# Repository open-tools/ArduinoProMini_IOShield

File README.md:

# ArduinoProMini_IOShield

Quick prototyping breakout board for Arduino Pro Mini with interface for NRF24L01+ and RFM69H wireless modules and breadboards and/or I²C connectors

## Inspiration
This board is inspired by the Arduino "Nano IO Shields" available for cheap at aliexpress (search for "arduino nano nrf24l01 board", e.g. [here](https://www.aliexpress.com/item/Free-shipping-Nano-328P-IO-wireless-sensor-expansion-board-for-XBEE-and-NRF24L01-Socket-for-arduino/32298692903.html)), which provide breakout pins, a connector for an NRF24L01+ module and an XBee module. 
As I don't have any use for the XBee socket, I simply broke off the header pins and instead taped a [tiny 5x11 pin breadboard](https://www.aliexpress.com/item/7Pcs-Mini-55-Points-Breadboard-Solderless-Prototype-Tie-point-For-Arduino-GM/32670910749.html) to the board. 

These boards are perfect for quick prototyping for the MySensors project for several reasons:
* you have the nrf24l01+ radio module already wired with their own voltage regulators and level shifters
* The board has its own power input and voltage regulators (VCC 5V will be fed to the Nano), so sensors with a high current requirement will get the power directly from the supply and not through the Arduino board.
* Each analog and digital pin has its own VCC+GND pins (usually when working with multiple sensors there is a severe shortage of VCC/GND pins for each sensor)
* The I²C and serial (RX/TX) lines are readily available as 1x4 pin headers (i.e. you don't need to know whether A4 or A5 is SDA or SCL).

The only drawback is that I use Pro Minis for most of my projects, so prototyping with a Nano means you are never testing the actual board in the prototype.

## The Board

This board provides 
* each pin of the Arduino Pro Mini as a pin header with its own VCC and GND 
* pads/connectors for a NRF24L01+ or a RFM69H wireless module (and solder pads for an XC6206 5V->3.3V regulator if required)
* I²C connector (VCC, GND, SCL, SDA)
* space for a tiny 55-pin mini breakout board or alternative three additional I²C breakout connections
* solder pads for its own AMS1117 voltage regulator
* ICSP connector to program the bootloader
* drills for the Arduino large enough to fit PogoPins, too, and
* the board outline and the holes are identical to the Arduino Uno, so Arduino holders can be used.

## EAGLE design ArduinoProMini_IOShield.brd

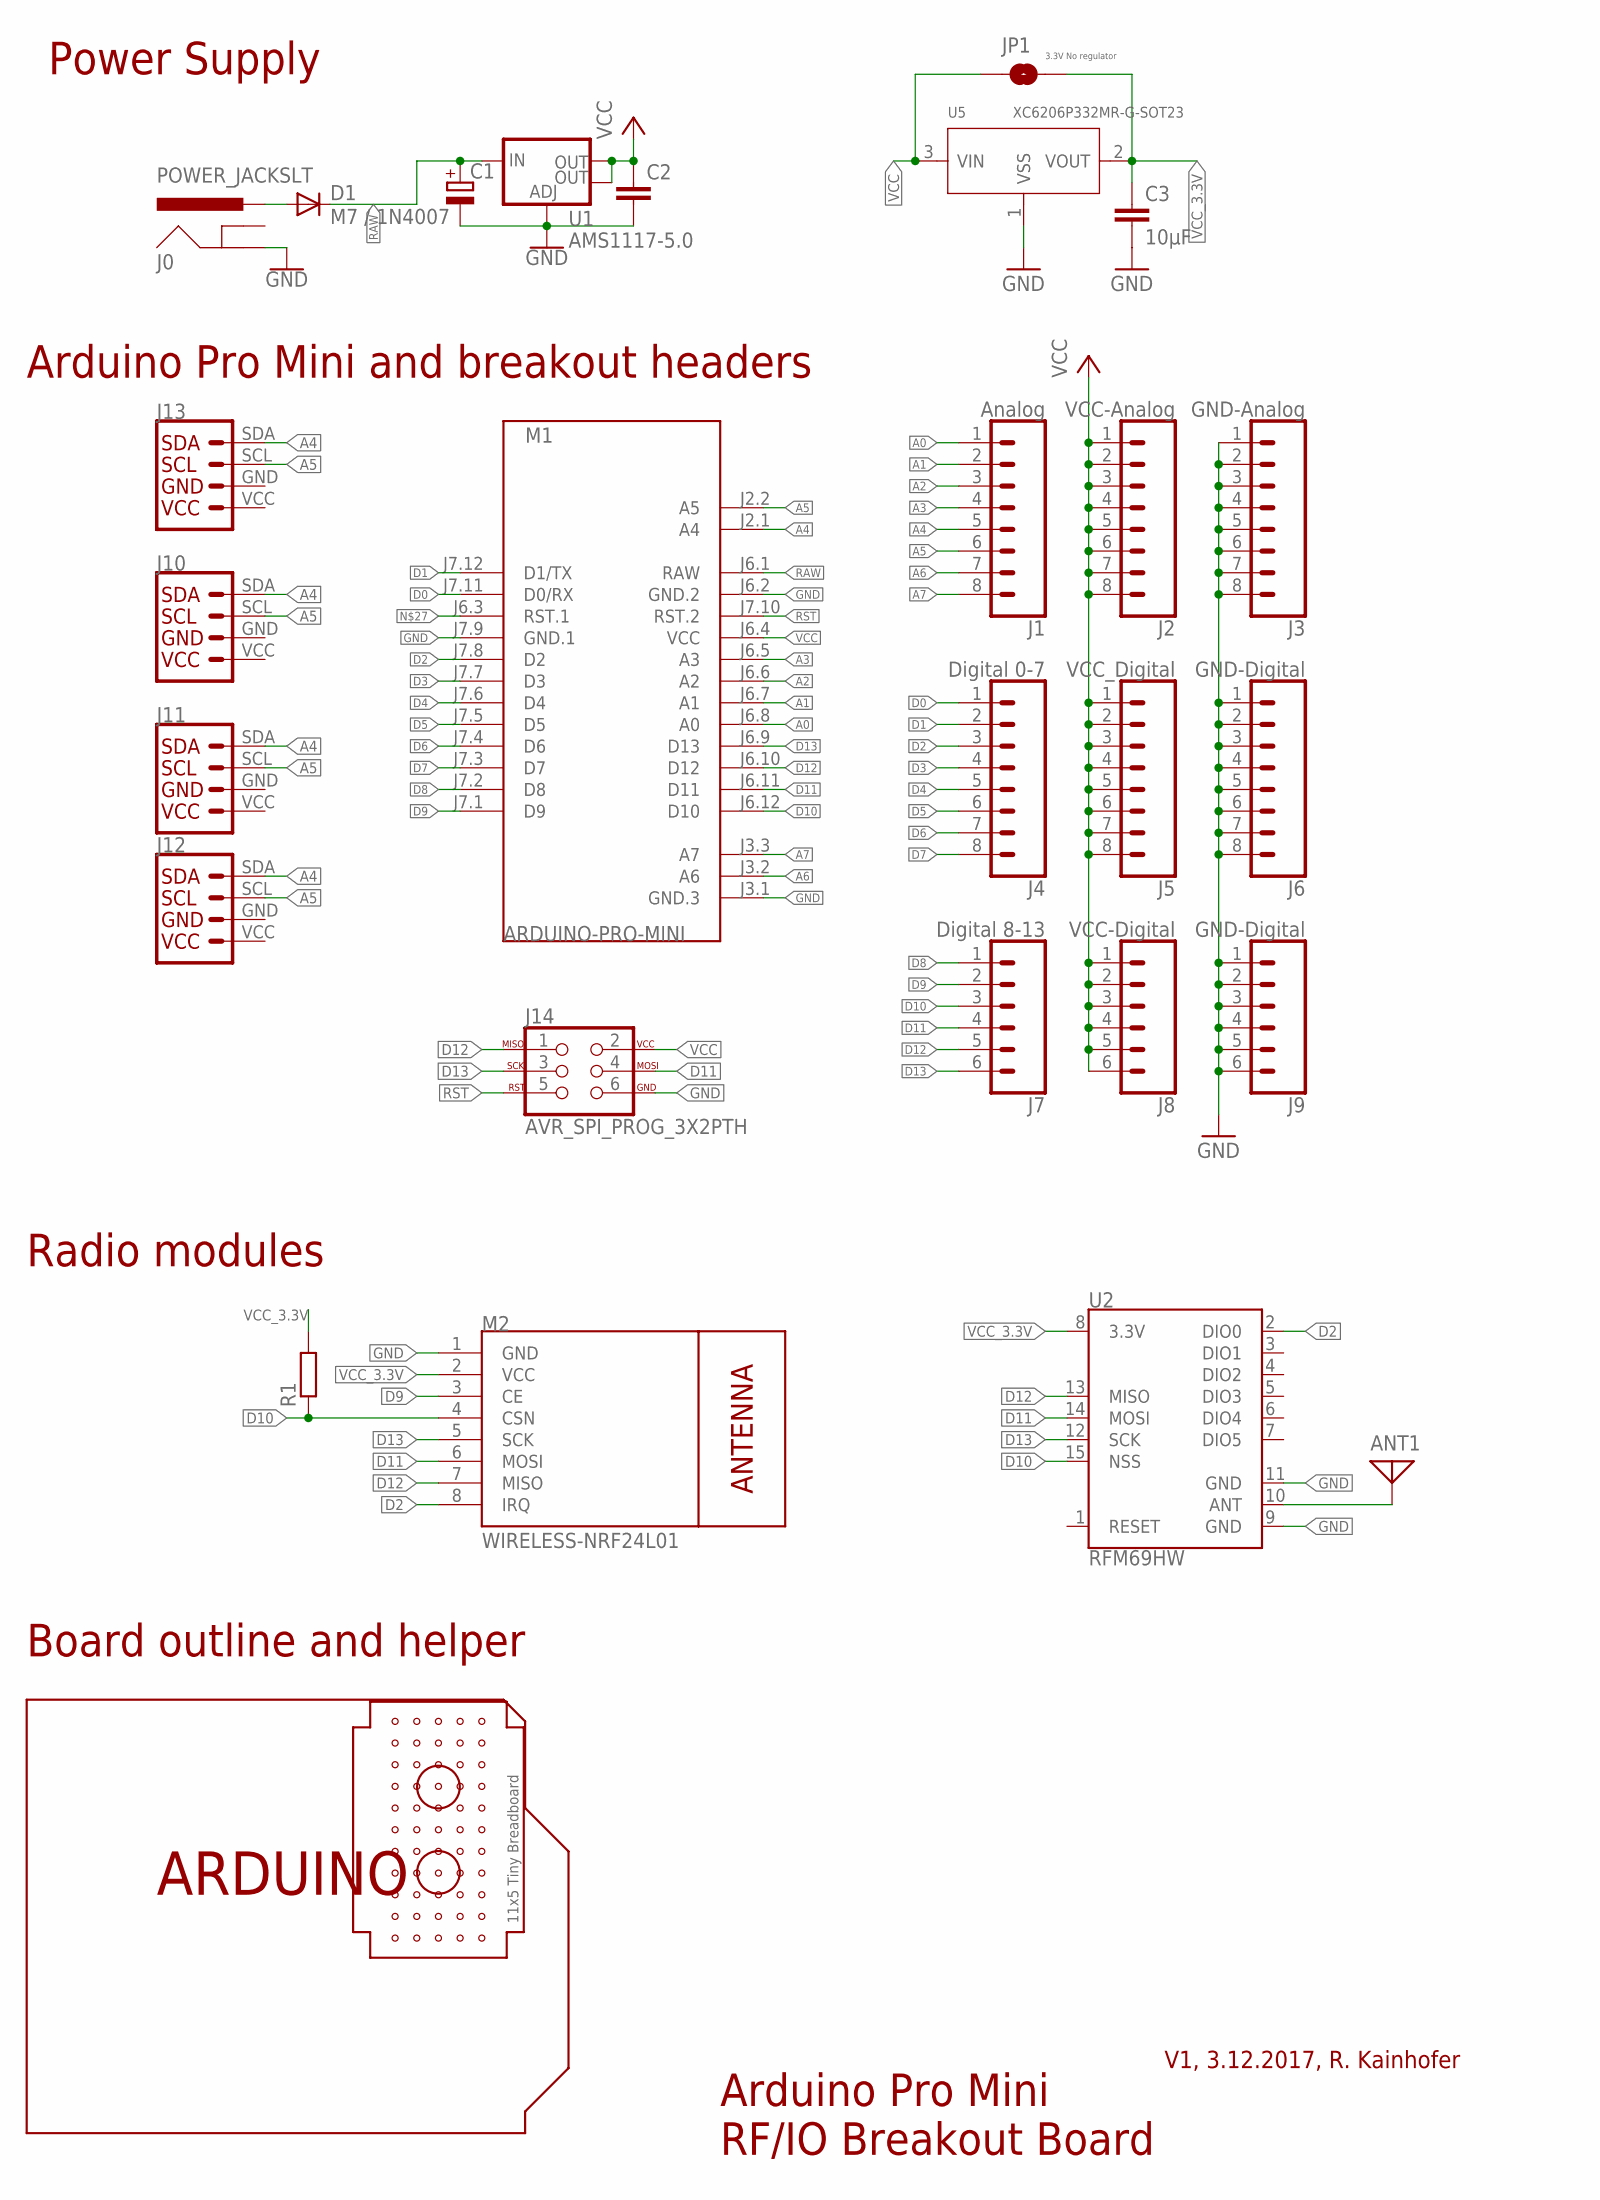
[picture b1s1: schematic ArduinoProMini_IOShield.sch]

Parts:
ANT1: ANTENNA; PAD-01
B1: ARDUINO_DIMENSION-DIMENSION; ARDUINOR3
C1: CPOL-EU153CLV-0605; 153CLV-0605
C2: C-EUC0805; C0805
C3: 10µF; C0805
D1: M7 / 1N4007; DO-214AC
J0: POWER_JACKSLT; POWER_JACK_SLOT
J1: Analog; 1X08
J2: VCC-Analog; 1X08
J3: GND-Analog; 1X08
J4: Digital 0-7; 1X08
J5: VCC_Digital; 1X08
J6: GND-Digital; 1X08
J7: Digital 8-13; 1X06
J8: VCC-Digital; 1X06
J9: GND-Digital; 1X06
J10, J11, J12, J13: I2C_CONN_VGLA; 1X04
J14: AVR_SPI_PROG_3X2PTH; 2X3
JP1: 3.3V No regulator; SMT-JUMPER_2_NO_SILK
M1: ARDUINO-PRO-MINI; ARDUINO-PRO-MINI#NP
M2: WIRELESS-NRF24L01
R1: R-EU_R0805; R0805
U1: AMS1117-5.0; SOT223
U2: RFM69HW; RFM69W-XXXS2
U5: XC6206P332MR-G-SOT23; SOT-23
U$1: MINI_BREADBOARD; MINI_BREADBOARD_11X5

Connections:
A0: J1.1, M1.J6.8 (A0)
A1: J1.2, M1.J6.7 (A1)
A2: J1.3, M1.J6.6 (A2)
A3: J1.4, M1.J6.5 (A3)
A4: J1.5, J10.SDA, J11.SDA, J12.SDA, J13.SDA, M1.J2.1 (A4)
A5: J1.6, J10.SCL, J11.SCL, J12.SCL, J13.SCL, M1.J2.2 (A5)
A6: J1.7, M1.J3.2 (A6)
A7: J1.8, M1.J3.3 (A7)
D0: J4.1, M1.J7.11 (D0/RX)
D1: J4.2, M1.J7.12 (D1/TX)
D2: J4.3, M1.J7.8 (D2), M2.8 (IRQ), U2.2 (DIO0)
D3: J4.4, M1.J7.7 (D3)
D4: J4.5, M1.J7.6 (D4)
D5: J4.6, M1.J7.5 (D5)
D6: J4.7, M1.J7.4 (D6)
D7: J4.8, M1.J7.3 (D7)
D8: J7.1, M1.J7.2 (D8)
D9: J7.2, M1.J7.1 (D9), M2.3 (CE)
D10: J7.3, M1.J6.12 (D10), M2.4 (CSN), R1.1, U2.15 (NSS)
D11: J7.4, J14.4, M1.J6.11 (D11), M2.6 (MOSI), U2.14 (MOSI)
D12: J7.5, J14.1, M1.J6.10 (D12), M2.7 (MISO), U2.13 (MISO)
D13: J7.6, J14.3, M1.J6.9 (D13), M2.5 (SCK), U2.12 (SCK)
GND: C1.-, C2.2, C3.2, J0.GND@2 (GND), J3.1, J3.2, J3.3, J3.4, J3.5, J3.6, J3.7, J3.8, J6.1, J6.2, J6.3, J6.4, J6.5, J6.6, J6.7, J6.8, J9.1, J9.2, J9.3, J9.4, J9.5, J9.6, J10.GND, J11.GND, J12.GND, J13.GND, J14.6, M1.J3.1 (GND.3), M1.J6.2 (GND.2), M1.J7.9 (GND.1), M2.1 (GND), U1.1 (ADJ), U2.9 (GND), U2.11 (GND), U5.1 (VSS)
unnamed: D1.A, J0.PWR
unnamed: ANT1.1, U2.10 (ANT)
RAW: C1.+, D1.C, M1.J6.1 (RAW), U1.3 (IN)
RST: J14.5, M1.J7.10 (RST.2)
VCC: C2.1, J2.1, J2.2, J2.3, J2.4, J2.5, J2.6, J2.7, J2.8, J5.1, J5.2, J5.3, J5.4, J5.5, J5.6, J5.7, J5.8, J8.1, J8.2, J8.3, J8.4, J8.5, J8.6, J10.VCC, J11.VCC, J12.VCC, J13.VCC, J14.2, JP1.1, M1.J6.4 (VCC), U1.2 (OUT), U1.4 (OUT), U5.3 (VIN)
VCC_3.3V: C3.1, JP1.2, M2.2 (VCC), R1.2, U2.8 (3.3V), U5.2 (VOUT)

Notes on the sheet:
Power Supply
Arduino Pro Mini and breakout headers
Radio modules
Board outline and helper
Arduino Pro Mini RF/IO Breakout Board
V1, 3.12.2017, R. Kainhofer

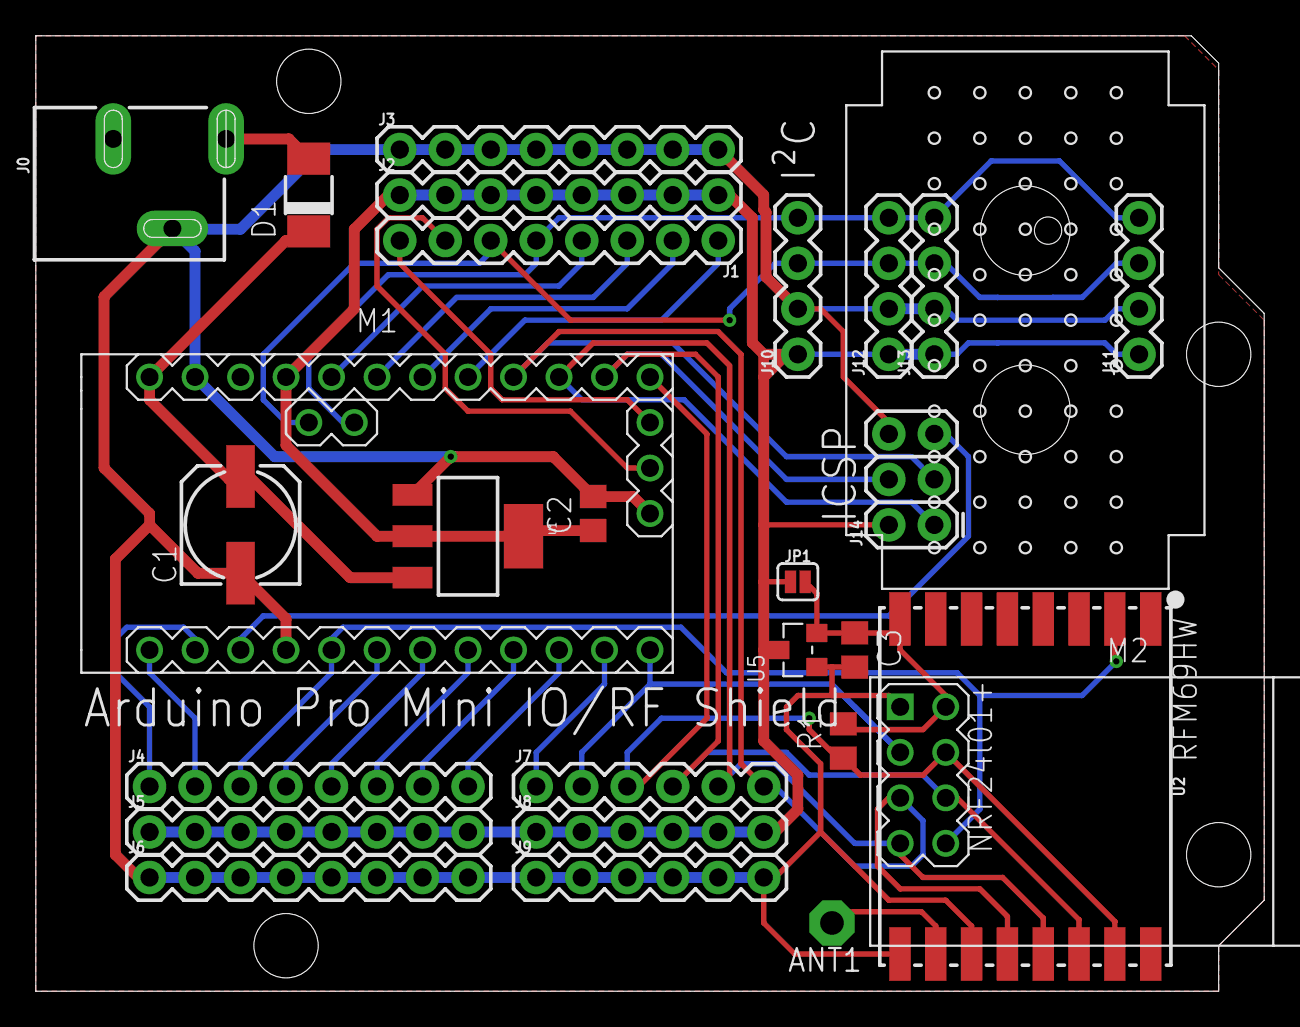
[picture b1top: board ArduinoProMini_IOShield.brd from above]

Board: 2 copper layers, 68.6 x 53.3 mm, 29 parts (0 on the bottom side), 29 nets.

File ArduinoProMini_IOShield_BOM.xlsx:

Ardiuno Pro Mini IO Shield – BOM
Qty | Value | Device | Package | Parts | Description | MF | MPN | Aliexpress or Ebay link
 |  |  | PAD-01 | ANT1
1 | 100µF | SMD capacitor, | 153CLV-0605 | C1
2 | 10µF | SMD capacitor 0805 | C0805 | C2, C3
1 | M7 / 1N4007 | SMD diode | DO-214AC | D1
1 |  | 5.5x2.1mm Power Jack | POWER_JACK_SLOT | J0
 | Analog | 2.54mm breakable male pin headers | 1X08 | J1
 | VCC-Analog |  | 1X08 | J2
 | GND-Analog |  | 1X08 | J3
 | Digital 0-7 |  | 1X08 | J4
 | VCC_Digital |  | 1X08 | J5
 | GND-Digital |  | 1X08 | J6
 | Digital 8-13 |  | 1X06 | J7
 | VCC-Digital |  | 1X06 | J8
 | GND-Digital |  | 1X06 | J9
 |  |  | 1X04 | J10
 |  |  | 1X04 | J11
 |  |  | 1X04 | J12
 |  |  | 1X04 | J13
 | AVR_SPI_PROG_3X2PTH |  | 2X3 | J14
 | 3.3V No regulator |  | SMT-JUMPER_2_NO_SILK | JP1
 | ARDUINO-PRO-MINI |  | ARDUINO-PRO-MINI#NP | M1
 | WIRELESS-NRF24L01 |  | WIRELESS-NRF24L01 | M2
 |  |  | R0805 | R1
 | AMS1117-5.0 |  | SOT223 | U1
 | RFM69HW |  | RFM69W-XXXS2 | U2
 | XC6206P332MR-G-SOT23 |  | SOT-23 | U5

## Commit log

2017-12-08 Board design
2017-12-08 Updated BOM
2017-12-09 Update README and BOM
2017-12-13 V0.2: Add power soldering connection, add altenative ProMini pinout, move ICSP header; Add pictures;
2017-12-13 Fix wrong images in readme

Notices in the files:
ArduinoProMini_IOShield.brd:
Licensed under teh CERN OHL v1.2
parts and their libraries:
diy-modules: Released under the Creative Commons Attribution 4.0 International License: http://creativecommons.org/licenses/by/4.0
SparkFun-Connectors: Licensing: Creative Commons ShareAlike 4.0 International - https://creativecommons.org/licenses/by-sa/4.0
